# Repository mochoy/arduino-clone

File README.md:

# arduino-clone
Eagle schematic and board files for custom Arduino clones

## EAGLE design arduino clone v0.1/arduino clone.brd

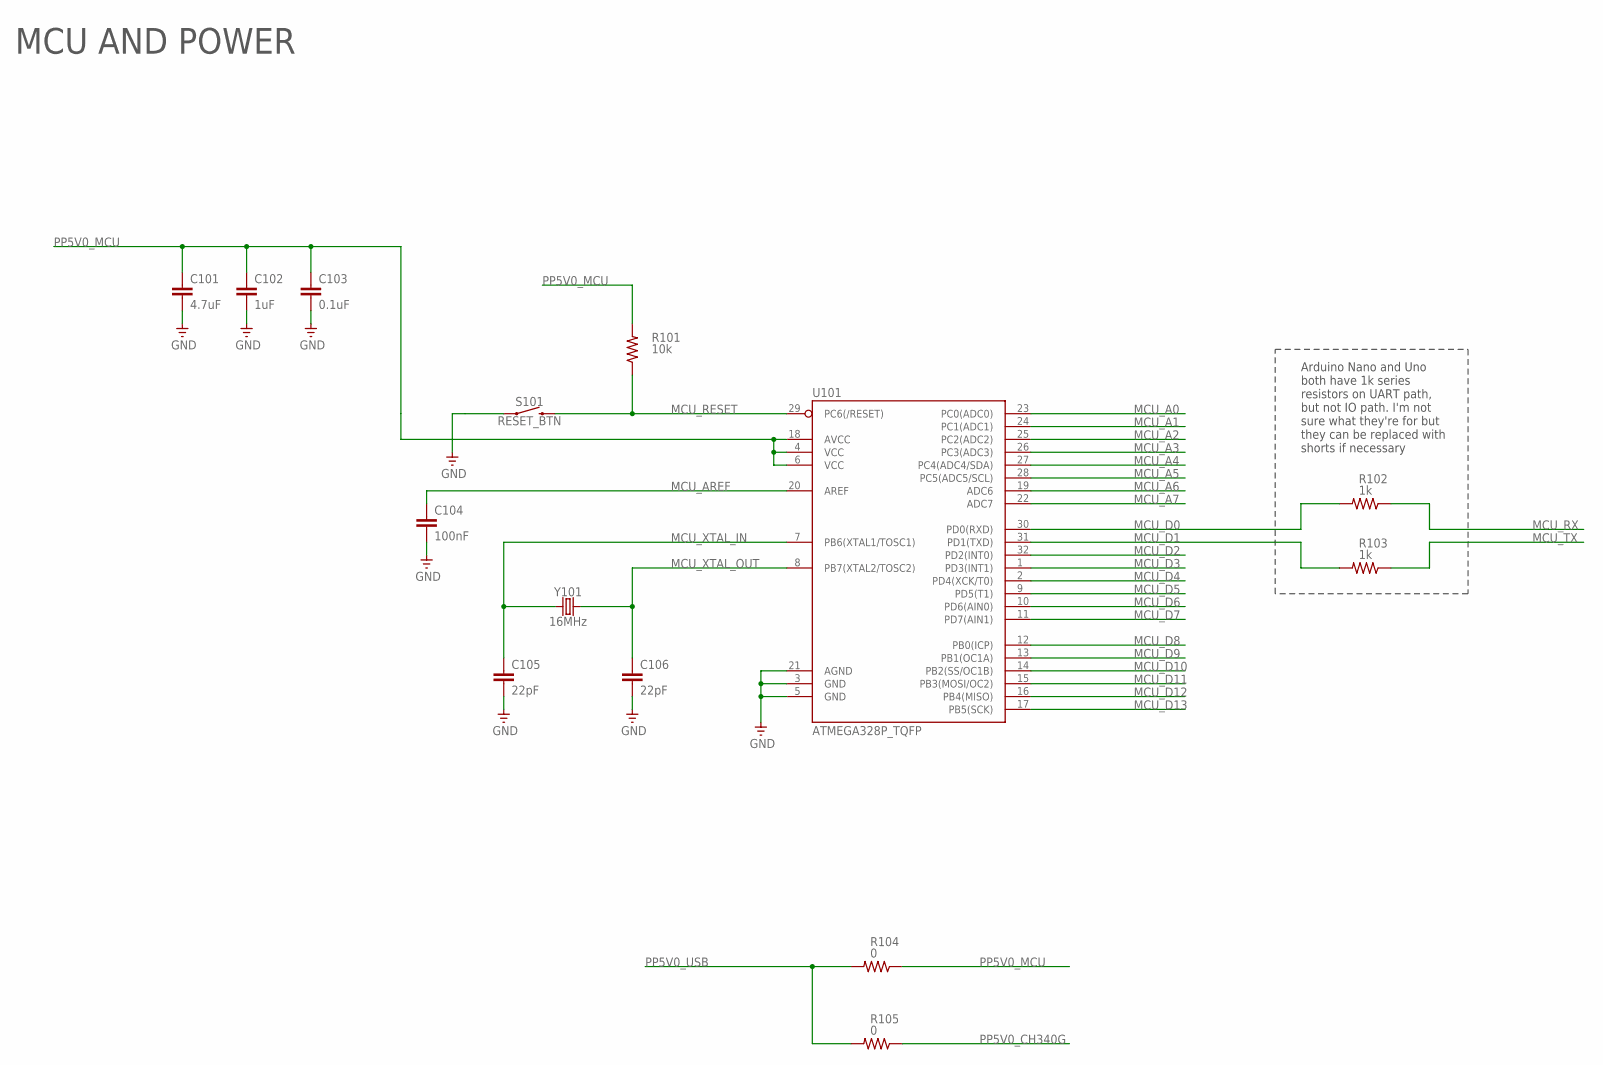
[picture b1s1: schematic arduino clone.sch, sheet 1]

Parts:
C101: 4.7uF; C0805
C102: 1uF; C0805
C103: 0.1uF; C0805
C104: 100nF; C0805
C105, C106: 22pF; C0805
R101: 10k; R0805
R102, R103: 1k; R0805
R104, R105: 0; R0805
S101: RESET_BTN; TACTILE_SWITCH_SMD_6.2MM_TALL
U101: ATMEGA328P_TQFP; TQFP32-08
Y101: 16MHz; CRYSTAL-SMD-5X3.2-4PAD

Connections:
GND: C101.2, C102.2, C103.2, C104.2, C105.2, C106.2, S101.A2 (1), U101.3 (GND), U101.5 (GND), U101.21 (AGND); also elsewhere on the board
MCU_A0: U101.23 (PC0(ADC0)); also elsewhere on the board
MCU_A1: U101.24 (PC1(ADC1)); also elsewhere on the board
MCU_A2: U101.25 (PC2(ADC2)); also elsewhere on the board
MCU_A3: U101.26 (PC3(ADC3)); also elsewhere on the board
MCU_A4: U101.27 (PC4(ADC4/SDA)); also elsewhere on the board
MCU_A5: U101.28 (PC5(ADC5/SCL)); also elsewhere on the board
MCU_A6: U101.19 (ADC6); also elsewhere on the board
MCU_A7: U101.22 (ADC7); also elsewhere on the board
MCU_AREF: C104.1, U101.20 (AREF); also elsewhere on the board
MCU_D0: R102.2, U101.30 (PD0(RXD)); also elsewhere on the board
MCU_D1: R103.2, U101.31 (PD1(TXD)); also elsewhere on the board
MCU_D2: U101.32 (PD2(INT0)); also elsewhere on the board
MCU_D3: U101.1 (PD3(INT1)); also elsewhere on the board
MCU_D4: U101.2 (PD4(XCK/T0)); also elsewhere on the board
MCU_D5: U101.9 (PD5(T1)); also elsewhere on the board
MCU_D6: U101.10 (PD6(AIN0)); also elsewhere on the board
MCU_D7: U101.11 (PD7(AIN1)); also elsewhere on the board
MCU_D8: U101.12 (PB0(ICP)); also elsewhere on the board
MCU_D9: U101.13 (PB1(OC1A)); also elsewhere on the board
MCU_D10: U101.14 (PB2(SS/OC1B)); also elsewhere on the board
MCU_D11: U101.15 (PB3(MOSI/OC2)); also elsewhere on the board
MCU_D12: U101.16 (PB4(MISO)); also elsewhere on the board
MCU_D13: U101.17 (PB5(SCK)); also elsewhere on the board
MCU_RESET: R101.1, S101.B2 (2), U101.29 (PC6(/RESET)); also elsewhere on the board
MCU_RX: R102.1; also elsewhere on the board
MCU_TX: R103.1; also elsewhere on the board
MCU_XTAL_IN: C105.1, U101.7 (PB6(XTAL1/TOSC1)), Y101.1
MCU_XTAL_OUT: C106.1, U101.8 (PB7(XTAL2/TOSC2)), Y101.3 (2)
PP5V0_CH340G: R105.1; also elsewhere on the board
PP5V0_MCU: C101.1, C102.1, C103.1, R101.2, R104.1, U101.4 (VCC), U101.6 (VCC), U101.18 (AVCC); also elsewhere on the board
PP5V0_USB: R104.2, R105.2; also elsewhere on the board

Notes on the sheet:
MCU AND POWER
Arduino Nano and Uno both have 1k series resistors on UART path, but not IO path. I'm not sure what they're for but they can be replaced with shorts if necessary

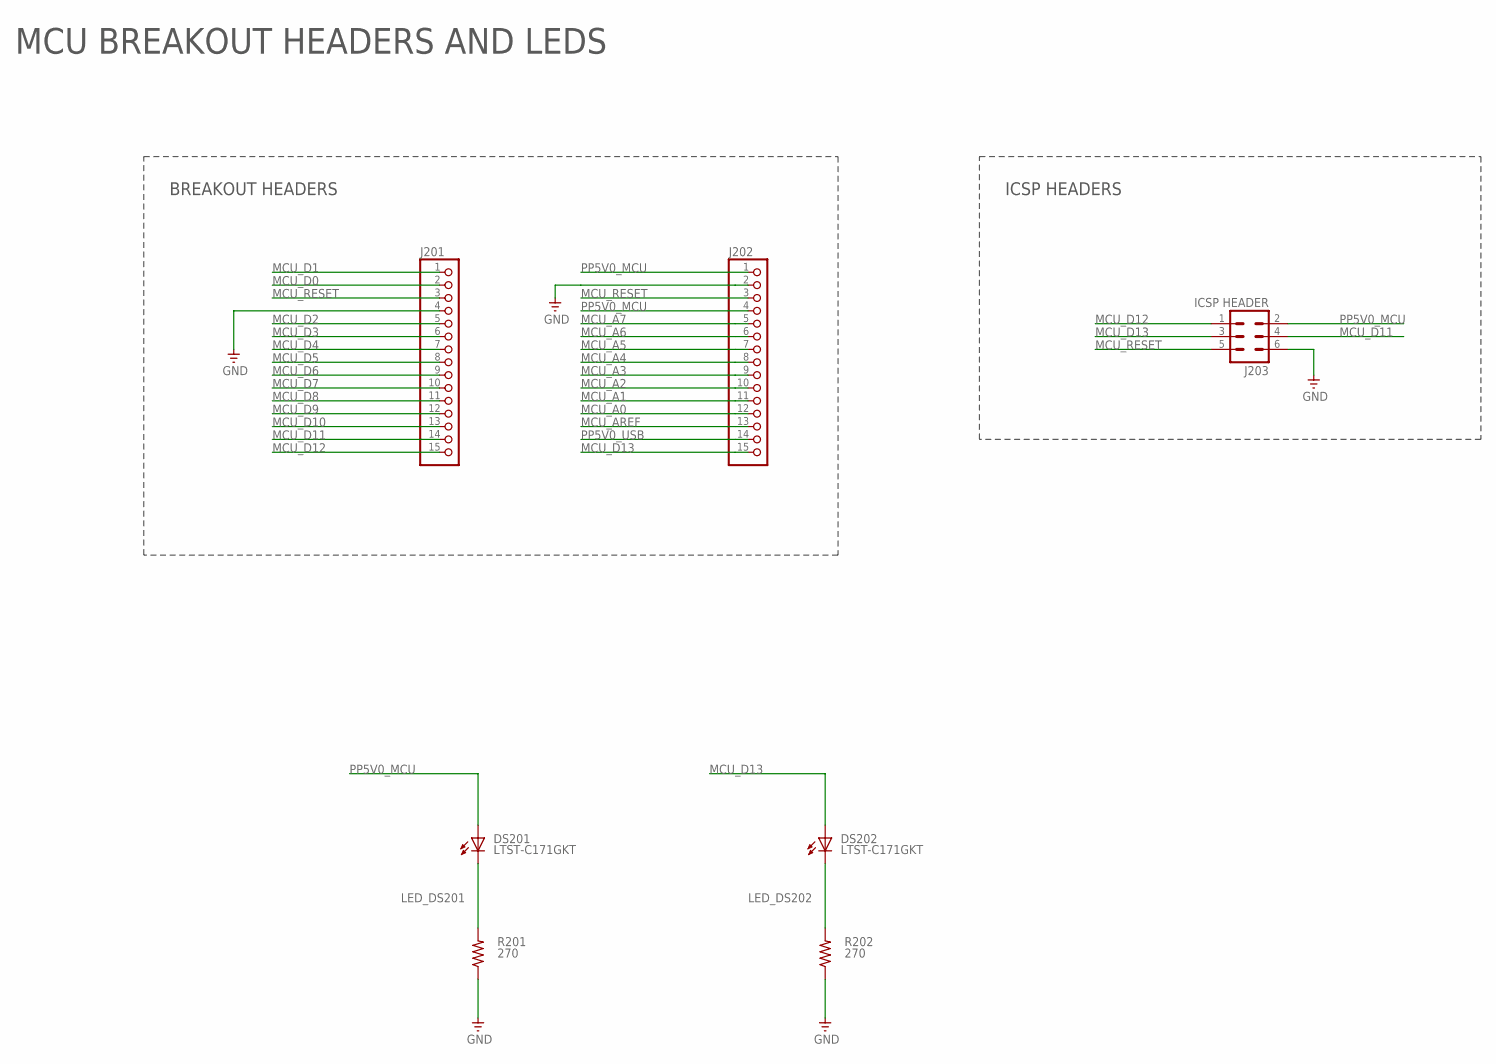
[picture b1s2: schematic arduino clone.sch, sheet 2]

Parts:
DS201, DS202: LTST-C171GKT; CHIPLED_0805
J201, J202: PINHD-1X15-CB; 1X15-CB
J203: ICSP HEADER; MA03-2
R201, R202: 270; M0805

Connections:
GND: J201.4, J202.2, J203.6, R201.1, R202.1; also elsewhere on the board
LED_DS201: DS201.C, R201.2
LED_DS202: DS202.C, R202.2
MCU_A0: J202.12; also elsewhere on the board
MCU_A1: J202.11; also elsewhere on the board
MCU_A2: J202.10; also elsewhere on the board
MCU_A3: J202.9; also elsewhere on the board
MCU_A4: J202.8; also elsewhere on the board
MCU_A5: J202.7; also elsewhere on the board
MCU_A6: J202.6; also elsewhere on the board
MCU_A7: J202.5; also elsewhere on the board
MCU_AREF: J202.13; also elsewhere on the board
MCU_D0: J201.2; also elsewhere on the board
MCU_D1: J201.1; also elsewhere on the board
MCU_D2: J201.5; also elsewhere on the board
MCU_D3: J201.6; also elsewhere on the board
MCU_D4: J201.7; also elsewhere on the board
MCU_D5: J201.8; also elsewhere on the board
MCU_D6: J201.9; also elsewhere on the board
MCU_D7: J201.10; also elsewhere on the board
MCU_D8: J201.11; also elsewhere on the board
MCU_D9: J201.12; also elsewhere on the board
MCU_D10: J201.13; also elsewhere on the board
MCU_D11: J201.14, J203.4; also elsewhere on the board
MCU_D12: J201.15, J203.1; also elsewhere on the board
MCU_D13: DS202.A, J202.15, J203.3; also elsewhere on the board
MCU_RESET: J201.3, J202.3, J203.5; also elsewhere on the board
PP5V0_MCU: DS201.A, J202.1, J202.4, J203.2; also elsewhere on the board
PP5V0_USB: J202.14; also elsewhere on the board

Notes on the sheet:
MCU BREAKOUT HEADERS AND LEDS
BREAKOUT HEADERS
ICSP HEADERS

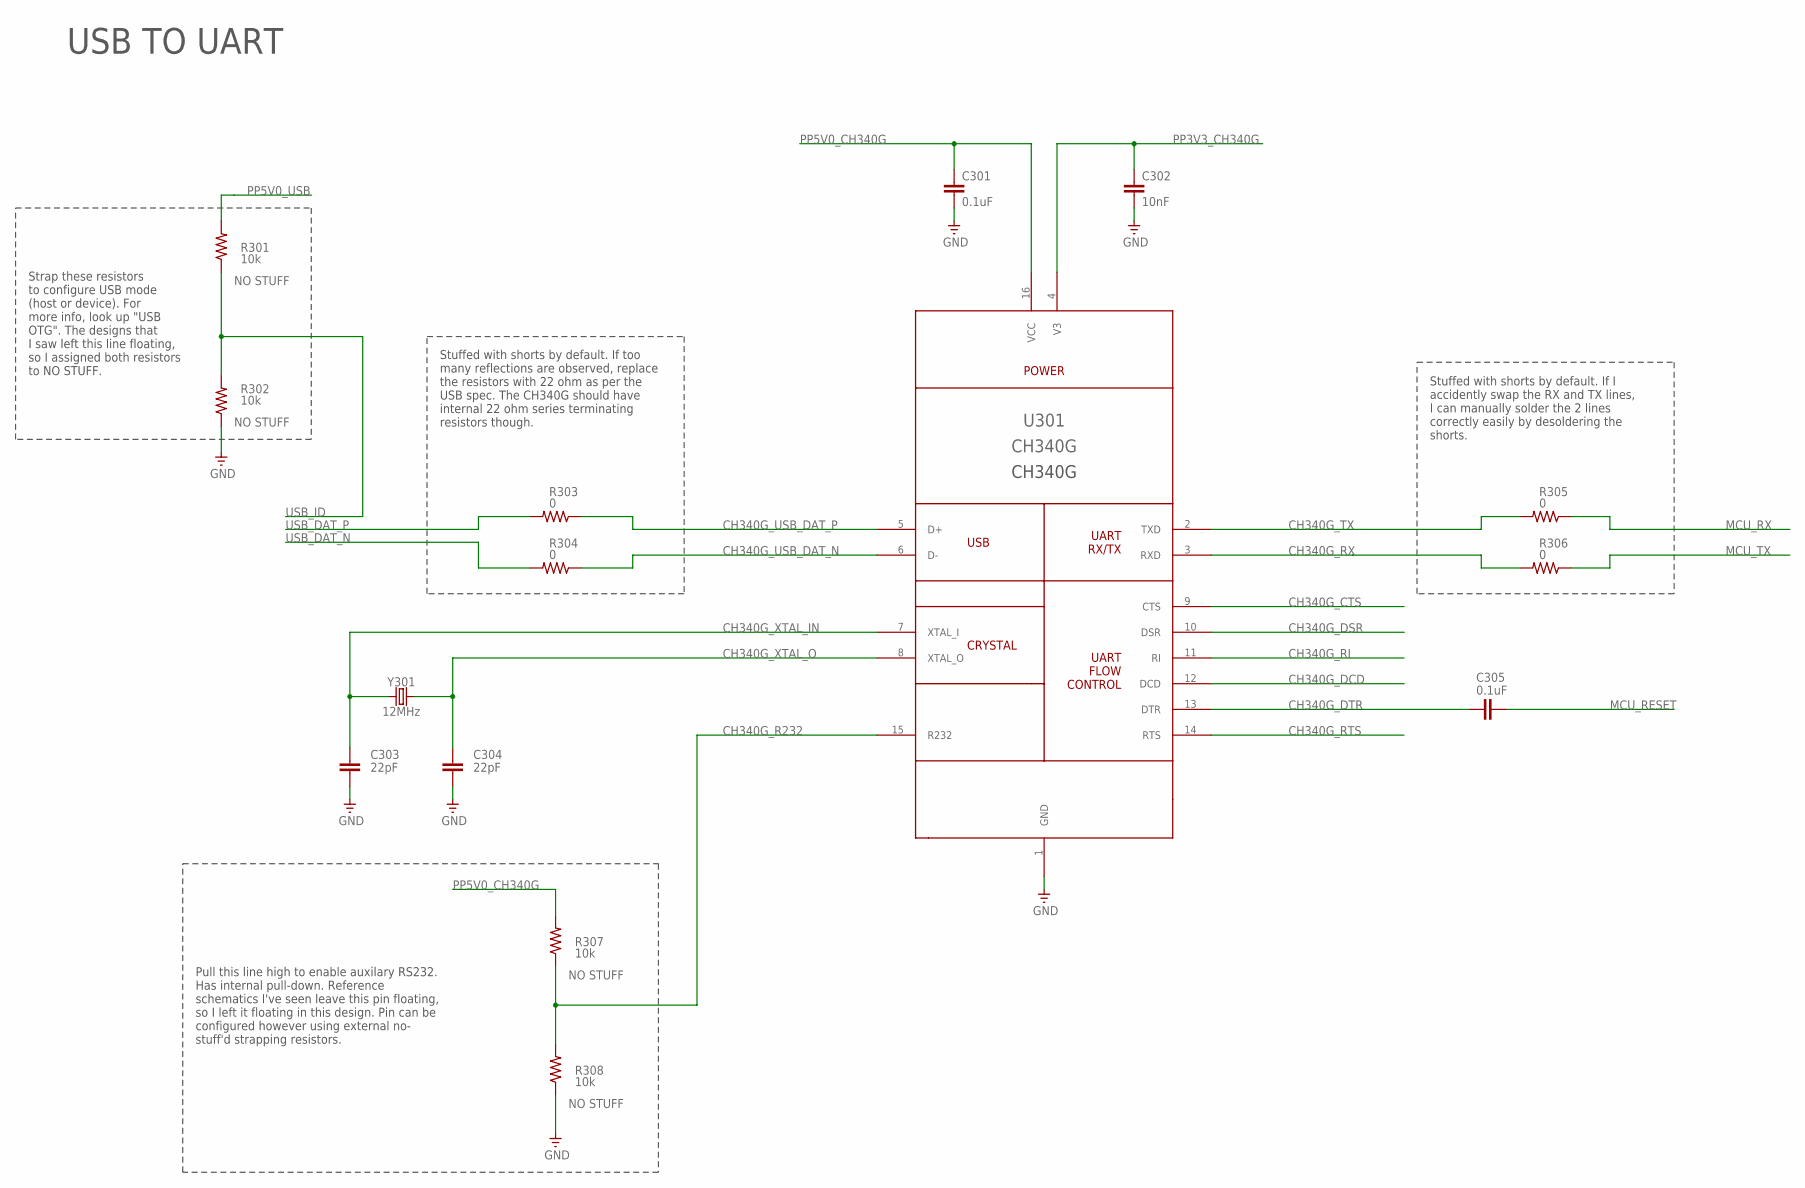
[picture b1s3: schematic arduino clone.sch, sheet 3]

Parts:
C301, C305: 0.1uF; C0805
C302: 10nF; C0805
C303, C304: 22pF; C0805
R301, R302, R307, R308: 10k; R0805
R303, R304, R305, R306: 0; R0805
U301: CH340G; SOIC16
Y301: 12MHz; CRYSTAL-SMD-5X3.2-4PAD

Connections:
CH340G_CTS: U301.9 (CTS); also elsewhere on the board
CH340G_DCD: U301.12 (DCD)
CH340G_DSR: U301.10 (DSR)
CH340G_DTR: C305.1, U301.13 (DTR)
CH340G_R232: R307.1, R308.2, U301.15 (R232)
CH340G_RI: U301.11 (RI)
CH340G_RTS: U301.14 (RTS)
CH340G_RX: R306.2, U301.3 (RXD)
CH340G_TX: R305.2, U301.2 (TXD)
CH340G_USB_DAT_N: R304.1, U301.6 (D-)
CH340G_USB_DAT_P: R303.1, U301.5 (D+)
CH340G_XTAL_IN: C303.1, U301.7 (XTAL_I), Y301.1
CH340G_XTAL_O: C304.1, U301.8 (XTAL_O), Y301.3 (2)
GND: C301.2, C302.2, C303.2, C304.2, R302.1, R308.1, U301.1 (GND); also elsewhere on the board
MCU_RESET: C305.2; also elsewhere on the board
MCU_RX: R305.1; also elsewhere on the board
MCU_TX: R306.1; also elsewhere on the board
PP3V3_CH340G: C302.1, U301.4 (V3)
PP5V0_CH340G: C301.1, R307.2, U301.16 (VCC); also elsewhere on the board
PP5V0_USB: R301.2; also elsewhere on the board
USB_DAT_N: R304.2; also elsewhere on the board
USB_DAT_P: R303.2; also elsewhere on the board
USB_ID: R301.1, R302.2; also elsewhere on the board

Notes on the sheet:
USB TO UART
Strap these resistors to configure USB mode (host or device). For more info, look up "USB OTG". The designs that I saw left this line floating, so I assigned both resistors to NO STUFF.
Stuffed with shorts by default. If too many reflections are observed, replace the resistors with 22 ohm as per the USB spec. The CH340G should have internal 22 ohm series terminating resistors though.
Stuffed with shorts by default. If I accidently swap the RX and TX lines, I can manually solder the 2 lines correctly easily by desoldering the shorts.
Pull this line high to enable auxilary RS232. Has internal pull-down. Reference schematics I've seen leave this pin floating, so I left it floating in this design. Pin can be configured however using external no- stuff'd strapping resistors.

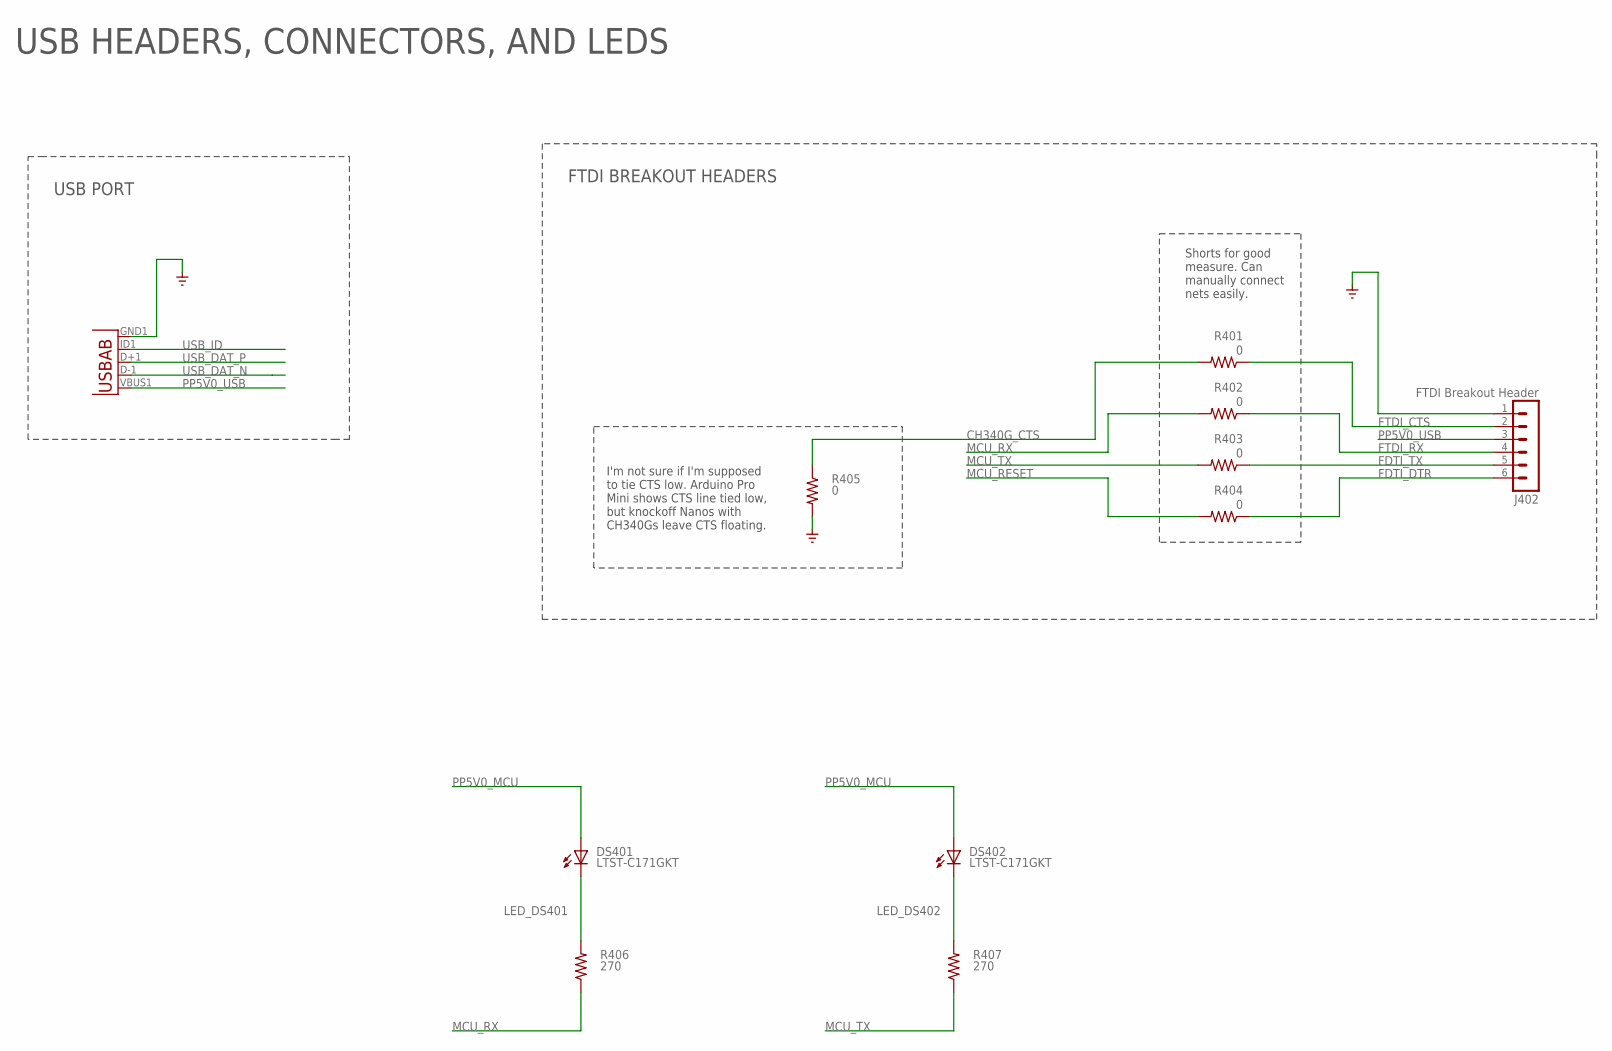
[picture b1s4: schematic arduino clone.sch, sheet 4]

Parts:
DS401, DS402: LTST-C171GKT; CHIPLED_0805
J401: USB-ABIN&OUT; USB-AB-MICRO-SMD-V03-IN&OUT
J402: FTDI Breakout Header; MA06-1
R401, R402, R403, R404, R405: 0; R0805
R406, R407: 270; M0805

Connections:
CH340G_CTS: R401.2, R405.1; also elsewhere on the board
FDTI_DTR: J402.6, R404.1
FDTI_TX: J402.5, R403.1
FTDI_CTS: J402.2, R401.1
FTDI_RX: J402.4, R402.1
GND: J401.GND1 (GND), J402.1, R405.2; also elsewhere on the board
LED_DS401: DS401.C, R406.2
LED_DS402: DS402.C, R407.2
MCU_RESET: R404.2; also elsewhere on the board
MCU_RX: R402.2, R406.1; also elsewhere on the board
MCU_TX: R403.2, R407.1; also elsewhere on the board
PP5V0_MCU: DS401.A, DS402.A; also elsewhere on the board
PP5V0_USB: J401.VBUS1 (VBUS), J402.3; also elsewhere on the board
USB_DAT_N: J401.D-1 (D-); also elsewhere on the board
USB_DAT_P: J401.D+1 (D+); also elsewhere on the board
USB_ID: J401.ID1 (USBID); also elsewhere on the board

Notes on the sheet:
USB HEADERS, CONNECTORS, AND LEDS
Shorts for good measure. Can manually connect nets easily.
I'm not sure if I'm supposed to tie CTS low. Arduino Pro Mini shows CTS line tied low, but knockoff Nanos with CH340Gs leave CTS floating.
USB PORT
FTDI BREAKOUT HEADERS

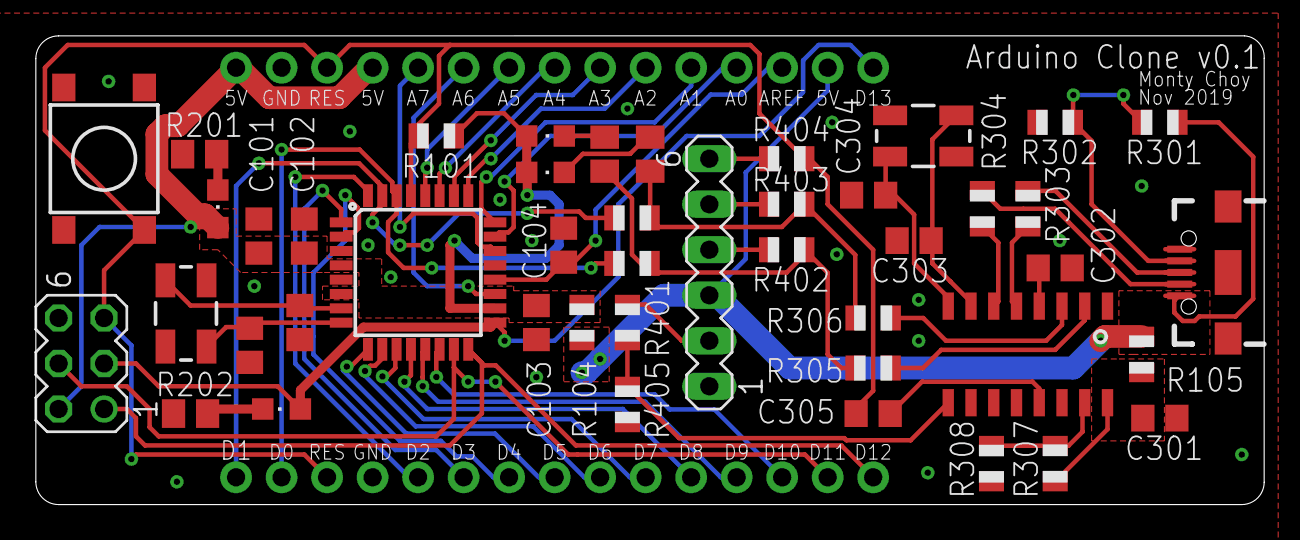
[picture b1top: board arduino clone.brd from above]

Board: 2 copper layers, 68.6 x 26.2 mm, 47 parts (0 on the bottom side), 53 nets.

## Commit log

2019-11-11 create schematic file for arduino clone
2019-11-11 add gitignore
2019-11-11 add pages for MCU and CH340G
2019-11-12 add atmega328p and CH340G ICs
2019-11-12 add title to MCU and USB to UART pages
2019-11-13 random eagle stuff
2019-11-14 connect VCC of MCU to PP5V0 rail
2019-11-15 connect gnd rails of MCU
2019-11-16 add decoupling caps to Arduino VCC rail
2019-11-16 add pullup to MCU reset
2019-11-16 add cap to aref pin
2019-11-16 add reset btn:
2019-11-18 add custom CH340G symbol
2019-11-18 add rail and rename CH340G
2019-11-19 add decoupling cap to 5V rail of CH340G
2019-11-19 connect gnd potential to CH340G
2019-11-19 add decoupling cap to PP3V3_CH340G rail
2019-11-19 add sparkfun micro USB port
2019-11-19 swap out USB for one used in Arduino Sparkfun pro mini
2019-11-19 connect gnd to usb port
2019-11-19 connect diff pair for USB
2019-11-19 add strapping resistors to ID of USB hub
2019-11-19 move strapping resistor ref des and value
2019-11-19 add power rail for USB
2019-11-19 add net name for USB ID pin
2019-11-19 add series termniation resistors for USB data diff pair
2019-11-19 add net names for diff pair on USB side
2019-11-19 add names for diff pair on CH340G side
2019-11-20 remove extra net on PP_USB rail
2019-11-20 add nostuff attribute to USB_ID net
2019-11-20 add descriptiont to strap USB_ID resistors
2019-11-20 move USB port and USB OTG strapping resistors
2019-11-21 add box around series termination resistors
2019-11-21 add note for series terminating resistors
2019-11-21 add RX and TX lines from CH340G
2019-11-21 add series resistors to UART lines
2019-11-21 add net names for AR UART lines on CH340G page
2019-11-21 connect AR_RX and TX to arduino
2019-11-22 add box around UART data resistors
2019-11-24 Add note for series resistors on RX and TX lines UART
2019-11-25 rename MCU nets to have 'mcu'
2019-11-25 add AC coupling cap on DTR line of CH340G
2019-11-25 disconnect USB nets from connector
2019-11-25 add signal nets to USB connector
2019-11-25 add named nets for CH350G UART flow control
2019-11-25 add FTDI breakout header
2019-11-25 add nets from FDTI headers to power and CTS
2019-11-25 add FTDI RX and TX lines
2019-11-25 add FTDI_DTR line
2019-11-25 connect MCU uart data lines to AR uart datalines
2019-11-25 add notes for FTDI breakout headers
2019-11-25 add note on CTS line
2019-11-25 update libs to fix R232 short pin
2019-11-25 add strapping resistors on CH340G_R323 pin
2019-11-25 ad notes to R232 strapping resistors
2019-11-25 add 22 pf caps for pierce oscillator
2019-11-25 add nets for crystal
2019-11-25 add and name crystal oscillator
2019-11-25 move RS232 strappig network higher up
2019-11-25 replace crystal with 12MHz as per CH340G spec
2019-11-25 rename caps on 5V0 MCU rail to apple naming convention
2019-11-25 rename rest of MCU components to apple naming convnetnion:
2019-11-25 add back RS232 strapping network that I accidently deleted
2019-11-25 update library to have new XTAL pin names
2019-11-25 update oscillator net names to XTA
2019-11-25 add pierce oscillator to MCU
2019-11-25 add net names for MCU XTAL
2019-11-25 move MCU nets out to give space for net names
2019-11-25 move XTAL and AREF decoupling components out to give space for net names
2019-11-26 add MCU analog port nets
2019-11-26 add 1k resistors on MCU UART lines
2019-11-26 connect UART lines to MCU_[UART]_R
2019-11-26 diverge FTDI header nets
2019-11-26 re-arragne resistor and note for CH340G_CTS
2019-11-26 rotate ref des and value for CTS strapping resistor
2019-11-26 add notes on MCU UART lines
2019-11-26 rename MCU pins to MCU_Dx and MCU uart lines
2019-11-26 rename all MCU_TX_R to MCU_TX
2019-11-26 add nets for port D pins
2019-11-26 add nets for pins on port B
2019-11-26 change a decoupling cap on 5V_MCU rail to 0.1uF
2019-11-26 center MCU stuff on page
2019-11-26 add page for MCU Breakout headers
2019-11-26 add page for USB connectors, headers, and LEDs
    rename MCU headers page to also include LEDs
2019-11-26 move USB port to page 4
2019-11-26 move FTDI breakout header to page 3
2019-11-26 center CH340G on page
2019-11-26 Re-add netnames on page 4
2019-11-26 rename everything on page 3 to have '3' prefix
2019-11-26 add boxes and labels for USB port and FTDI breakout headers
2019-11-26 page 1 also dedicated to power
2019-11-26 move MCU stuff up to give space for power stuff below on same page
2019-11-26 add resistors for power stuff
2019-11-26 add ICSP header
2019-11-26 add breakout headers
2019-11-26 connect left breakout header
2019-11-26 connect breakout headers for right breakout headers
2019-11-26 add and label box around breakout headers
2019-11-26 connect up ICSP headers
2019-11-26 add box and label for ICSP headers
2019-11-26 create board from schemtaic
2019-11-26 add LED on 5V MCU rail
2019-11-26 add LED on pin 13
2019-11-26 D13 LED sources from D13
2019-11-26 add debug LEDs for UART data lines
2019-11-26 place headers, ICs, and USB port
2019-11-26 rename neg USB diff pair with 'N' prefix
2019-11-27 define netclass for USB data diff paris
2019-11-27 rename USB diff pairs so they're recognized by eagle
2019-11-27 assign net class to USB diff pair
2019-11-27 rename diff pair on USB side so eagle can detect it
2019-11-27 extend left side traces on CH340G to give space for longer USB data names
2019-11-27 USB diff pair net class now 10mil trace width
2019-11-27 assign USB diff pair on CH340G side to USB diff pair net class
2019-11-27 route USB diff pair on CH340G side
2019-11-27 route USB diff pair on USB port side
2019-11-27 route traces for crystal CH340G
2019-11-27 move CH340G crystal capacitor as suggested in microchip document
2019-11-27 move CH340G crystal lines away from USB dat lines
2019-11-27 place and route MCU oscillator
2019-11-27 move crystal and caps closer to CH340G
2019-11-27 move USB diff pair routing to give space for 3.3V docoupling cap
2019-11-27 place and route USB_ID strapping resistors
2019-11-27 place and route TX and RX from CH340G
2019-11-27 place and route resistors between CH340G and FTDI headers
2019-11-27 place and route UART debug LEDs
2019-11-27 place decoupling caps for MCU power
2019-11-27 add shape for PP5V0_MCU
2019-11-27 refine PP5V0_MCU shape
2019-11-27 extend PP5V0_MCU shape to hit another nearby pin
2019-11-27 place and route decoupling cap C104
2019-11-27 add top gnd place
2019-11-27 route UART RX and TX lines to MCU
2019-11-27 place and route power indicator LED
2019-11-27 place CH340G power series reisistor
2019-11-27 add shape for PP5V0_USB
2019-11-27 add shape for PP5V0_CH340G
2019-11-27 add trace from FTDI header to resistor
2019-11-28 place and route D13 LED
2019-11-28 place R104 and extend PP5V)_USB shape to hit it
2019-11-28 rotate C104 180 deg to give space to other stuff
2019-11-28 move R104 to right of MCU, close off PP5V0_MCU plane to left of MCU
2019-11-28 move series UART resistors down
2019-11-28 place and route UART LEDs
2019-11-28 smash UART LED resistor ref des
2019-11-28 move UART resistors and LEDs up to give space for MCU power decouoling
2019-11-28 move C103 and R104 and MCU power shape over to left
2019-11-28 move and route FTDI CTS resistors
2019-11-28 route PP5V0_USB from MCU to FTDI header
2019-11-28 move decoupling caps on left side of MCU closer to MCU
2019-11-28 expand PP5V0_MCU shape to traverse accross IC and hit moth sides of MCU
2019-11-28 move and redo PP5V0_MCU shape on left of MCU
2019-11-28 move and reroute R201
2019-11-28 route trace from D13 to LED
2019-11-28 redo CH340G_R232 trace to set trace between R308 and R307 to that net
2019-11-28 move and re-route R201
2019-11-28 route SPI lines to ICSP headers
2019-11-28 ICSP header now connects power to PP5V0_MCU
2019-11-28 route PP5V0_MCU to ICSP header
2019-11-28 place and route R101
2019-11-28 route PP5V0_MCU to UART LEDs
2019-11-28 route analog pins 2-5
2019-11-28 connect rest of analog pins
2019-11-28 palce and route C305
2019-11-28 route reset signals
2019-11-28 route MCU_AREF
2019-11-28 route and place R308 and R307
2019-11-28 add PP5V0_USB trace from USB port to FTDI header
2019-11-28 add D13 trace from MCU to header
2019-11-28 add thicker traces for PP5V0_USB to headers
2019-11-28 headers connect to PP5V0_MCU instead of PP5V0_USB
2019-11-28 route PP5V0_MCU to headers
2019-11-28 route D0,1,3
2019-11-28 route D3 and D4
2019-11-28 reroute D2 and D3
2019-11-28 route rest of Digital pins
2019-11-28 route PP5V0_USB to pullup R301
2019-11-28 approve DRCs with USB port
2019-11-29 move around traces to shrink board outline
2019-11-29 round corners
2019-11-29 add gnd plane on bottom
2019-11-29 add gnd vias so gnd hits everything
2019-11-29 add shape for PP5V0_USB to MCU
2019-11-29 remove wire stubs
2019-11-29 add more gnd vias to push gnd plane out
2019-11-29 move ref des of R301 and R302 down to give space for txt aboce
2019-11-29 add project title, name, and date
2019-11-29 add txt for bottom row of headers
2019-11-29 add text to top headers
2019-11-29 move gnd via so it doesn't block txt
2019-11-29 add 50 mil 5V trace
2019-11-29 expand 5V power plane that runs under MCU IC
2019-11-29 move R301 pullup trace for better gnd path from USB port
2019-11-29 re-route USB_ID trace for better gnd coverage
2019-11-29 add more random gnd vias
2019-11-29 generate gerbers for v0.1
2020-01-02 generate pdf schematics
2020-04-21 regenerate gerbers that include drill file

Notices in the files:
parts and their libraries:
SparkFun-Switches: Licensing: Creative Commons ShareAlike 4.0 International - https://creativecommons.org/licenses/by-sa/4.0
